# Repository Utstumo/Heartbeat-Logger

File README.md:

# Heartbeat-Logger
A small, portable device that will continuously log your ECG - the "waveform" of your heart - onto a memory card for analysis.

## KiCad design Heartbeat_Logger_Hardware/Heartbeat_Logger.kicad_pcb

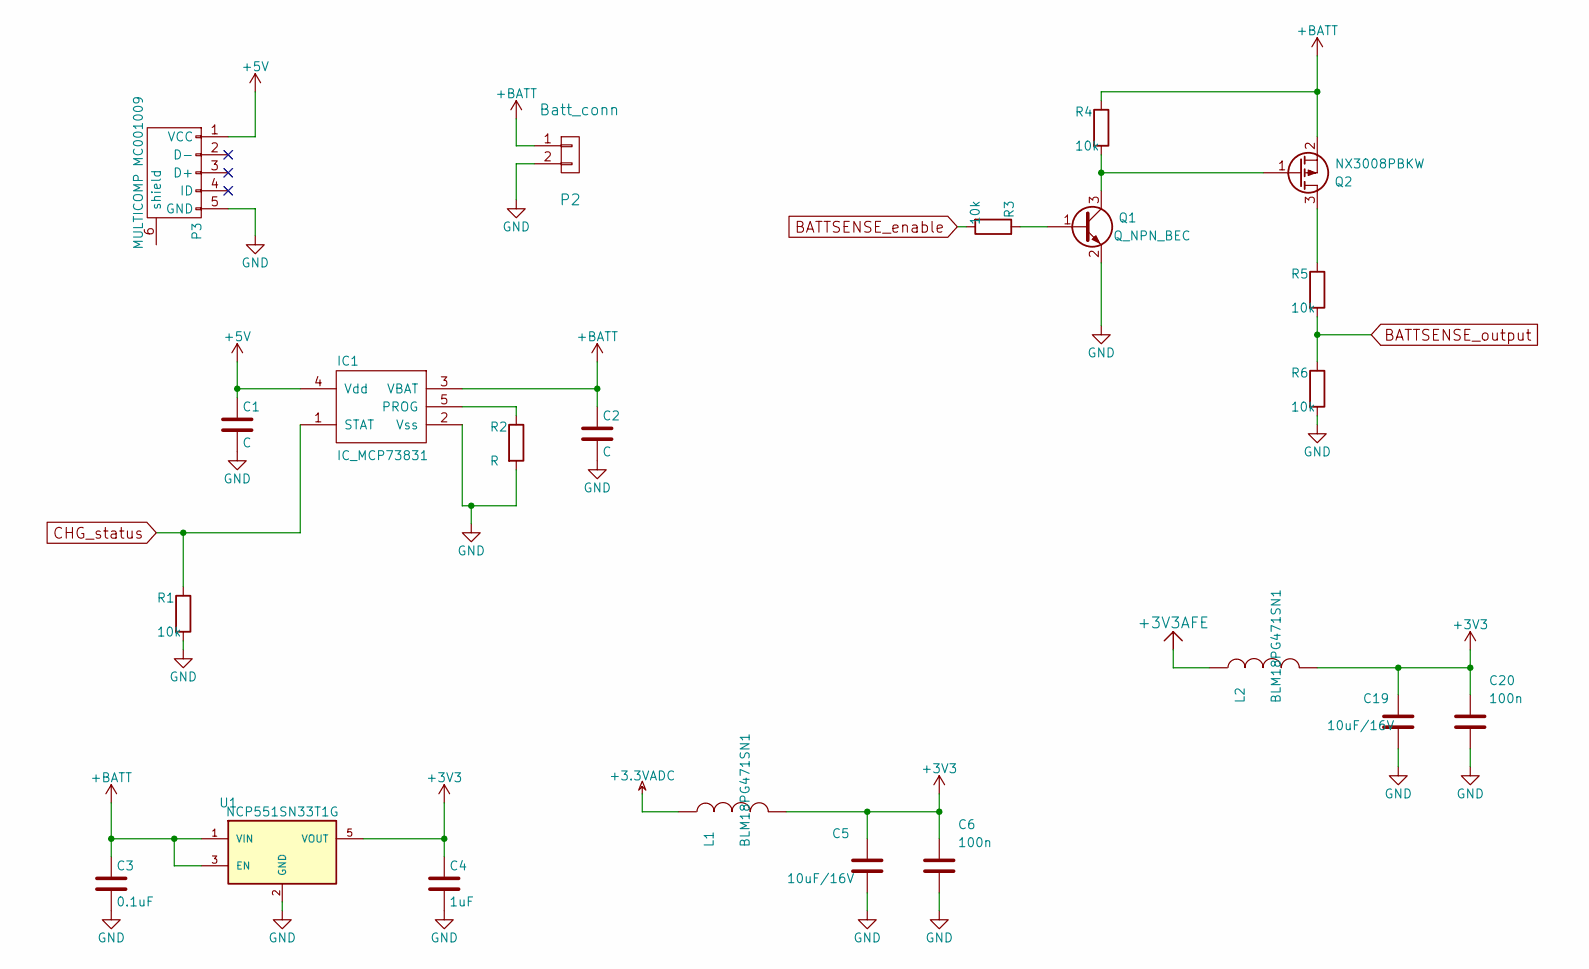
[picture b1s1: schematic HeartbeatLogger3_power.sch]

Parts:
C1, C2: C; C_0603_HandSoldering
C3: 0.1uF; C_0603_HandSoldering
C4: 1uF; C_0603_HandSoldering
C5, C19: 10uF/16V; C_0603_HandSoldering
C6, C20: 100n; C_0603_HandSoldering
IC1: IC_MCP73831; SOT-23-5
L1, L2: BLM18PG471SN1; R_0603_HandSoldering
P2: Batt_conn; Wire_terminal_x2
P3: MULTICOMP MC001009; Multicomp_MC001009_handsolder
Q1: Q_NPN_BEC
Q2: NX3008PBKW; SOT-323
R1, R3, R4, R5, R6: 10k; R_0603_HandSoldering
R2: R; R_0603_HandSoldering
U1: NCP551SN33T1G; SOT-23-5

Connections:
+3.3VADC: L1.1; also elsewhere on the board
+3V3: C4.1, C5.1, C6.1, C19.1, C20.1, L1.2, L2.2, U1.5 (VOUT); also elsewhere on the board
+3V3AFE: L2.1; also elsewhere on the board
+5V: C1.1, IC1.4 (Vdd), P3.1 (VCC)
+BATT: C2.1, C3.1, IC1.3 (VBAT), P2.1, Q2.2 (S), R4.1, U1.1 (VIN), U1.3 (EN)
BATTSENSE_enable: R3.2; also elsewhere on the board
BATTSENSE_output: R5.2, R6.1; also elsewhere on the board
CHG_status: IC1.1 (STAT), R1.1; also elsewhere on the board
GND: C1.2, C2.2, C3.2, C4.2, C5.2, C6.2, C19.2, C20.2, IC1.2 (Vss), P2.2, P3.5 (GND), Q1.2 (E), R1.2, R2.2, R6.2, U1.2 (GND); also elsewhere on the board
unnamed: IC1.5 (PROG), R2.1
unnamed: Q1.1 (B), R3.1
unnamed: Q1.3 (C), Q2.1 (G), R4.2
unnamed: Q2.3 (D), R5.1

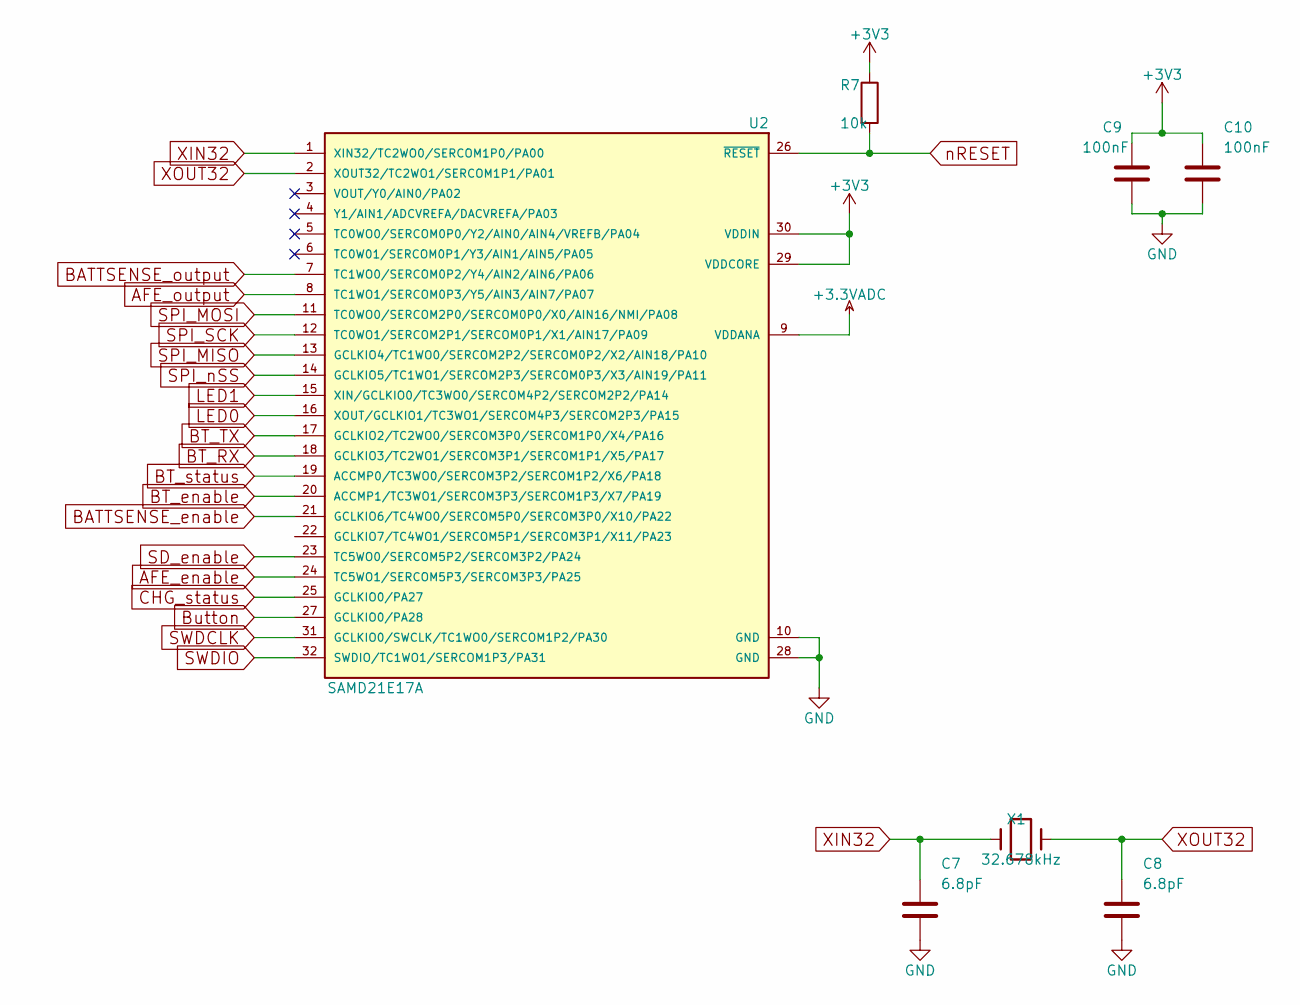
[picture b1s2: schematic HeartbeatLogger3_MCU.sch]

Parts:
C7, C8: 6.8pF; C_0603_HandSoldering
C9, C10: 100nF; C_0603_HandSoldering
R7: 10k; R_0603_HandSoldering
U2: SAMD21E17A; SAMD21_QFP_32_handsolder
X1: XTAL-32.768kHz-Cilindrical-SMD; ABS07-32.768KHZ-T

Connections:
+3.3VADC: U2.9 (VDDANA); also elsewhere on the board
+3V3: C9.1, C10.1, R7.1, U2.29 (VDDCORE), U2.30 (VDDIN); also elsewhere on the board
AFE_enable: U2.24 (TC5WO1/SERCOM5P3/SERCOM3P3/PA25); also elsewhere on the board
AFE_output: U2.8 (TC1WO1/SERCOM0P3/Y5/AIN3/AIN7/PA07); also elsewhere on the board
BATTSENSE_enable: U2.21 (GCLKIO6/TC4WO0/SERCOM5P0/SERCOM3P0/X10/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); also elsewhere on the board
BATTSENSE_output: U2.7 (TC1WO0/SERCOM0P2/Y4/AIN2/AIN6/PA06); also elsewhere on the board
BT_RX: U2.18 (GCLKIO3/TC2WO1/SERCOM3P1/SERCOM1P1/X5/P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); also elsewhere on the board
BT_TX: U2.17 (GCLKIO2/TC2WO0/SERCOM3P0/SERCOM1P0/X4/P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); also elsewhere on the board
BT_enable: U2.20 (ACCMP1/TC3WO1/SERCOM3P3/SERCOM1P3/X7/PA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); also elsewhere on the board
BT_status: U2.19 (ACCMP0/TC3WO0/SERCOM3P2/SERCOM1P2/X6/PA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); also elsewhere on the board
Button: U2.27 (GCLKIO0/PA28); also elsewhere on the board
CHG_status: U2.25 (GCLKIO0/PA27); also elsewhere on the board
GND: C7.2, C8.2, C9.2, C10.2, U2.10 (GND), U2.28 (GND); also elsewhere on the board
LED0: U2.16 (XOUT/GCLKIO1/TC3WO1/SERCOM4P3/SERCOM2P3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); also elsewhere on the board
LED1: U2.15 (XIN/GCLKIO0/TC3WO0/SERCOM4P2/SERCOM2P2/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); also elsewhere on the board
SD_enable: U2.23 (TC5WO0/SERCOM5P2/SERCOM3P2/PA24); also elsewhere on the board
SPI_MISO: U2.13 (GCLKIO4/TC1WO0/SERCOM2P2/SERCOM0P2/X2/A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); also elsewhere on the board
SPI_MOSI: U2.11 (TC0WO0/SERCOM2P0/SERCOM0P0/X0/AIN16/NMI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); also elsewhere on the board
SPI_SCK: U2.12 (TC0WO1/SERCOM2P1/SERCOM0P1/X1/AIN17/PA09); also elsewhere on the board
SPI_nSS: U2.14 (GCLKIO5/TC1WO1/SERCOM2P3/SERCOM0P3/X3/A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); also elsewhere on the board
SWDCLK: U2.31 (GCLKIO0/SWCLK/TC1WO0/SERCOM1P2/PA30); also elsewhere on the board
SWDIO: U2.32 (SWDIO/TC1WO1/SERCOM1P3/PA31); also elsewhere on the board
XIN32: C7.1, U2.1 (XIN32/TC2WO0/SERCOM1P0/PA00), X1.1
XOUT32: C8.1, U2.2 (XOUT32/TC2WO1/SERCOM1P1/PA01), X1.2
nRESET: R7.2, U2.26 (~RESET~); also elsewhere on the board

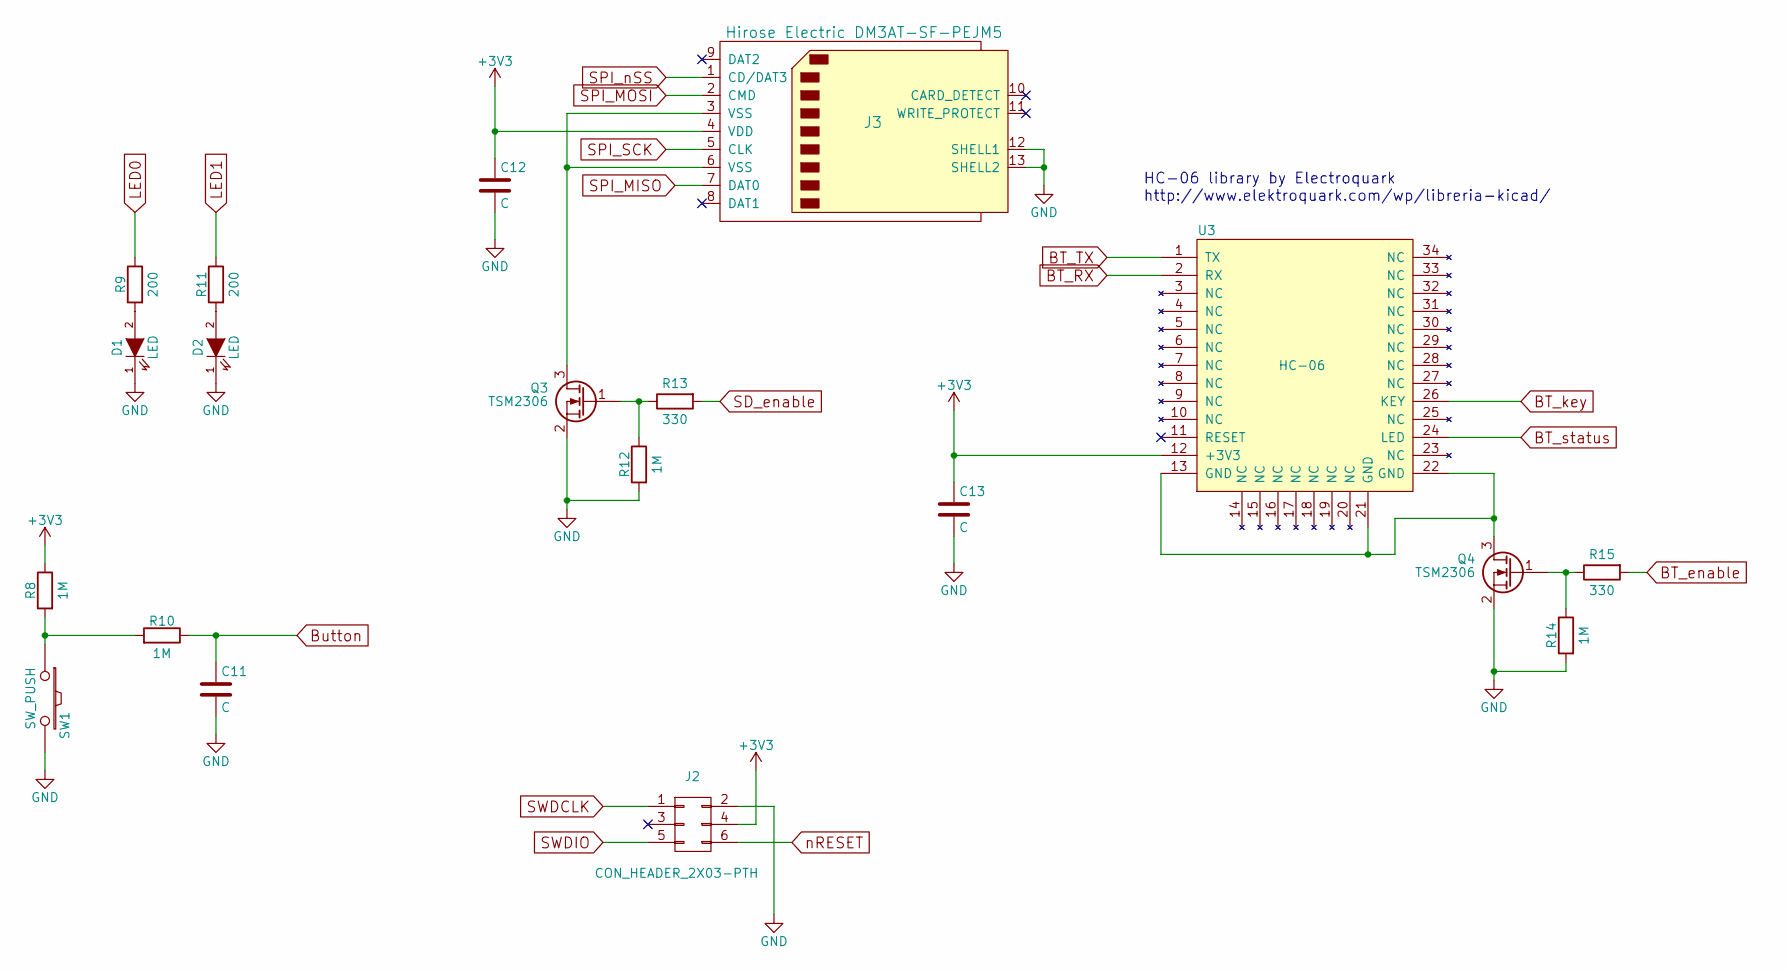
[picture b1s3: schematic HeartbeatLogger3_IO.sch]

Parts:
C11, C12, C13: C; C_0603_HandSoldering
D1, D2: LED; R_0603_HandSoldering
J2: CON_HEADER_2X03-PTH; Pin_Header_Straight_2x03
J3: Hirose Electric DM3AT-SF-PEJM5; Hirose_Electric_DM3AT-SF-PEJM5_handsolder
Q3, Q4: TSM2306; SOT-23
R8, R10, R12, R14: 1M; R_0603_HandSoldering
R9, R11: 200; R_0603_HandSoldering
R13, R15: 330; R_0603_HandSoldering
SW1: SW_PUSH; MC32882
U3: HC-06

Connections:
+3V3: C12.1, C13.1, J2.4, J3.4 (VDD), R8.1, U3.12 (+3V3); also elsewhere on the board
BT_RX: U3.2 (RX); also elsewhere on the board
BT_TX: U3.1 (TX); also elsewhere on the board
BT_enable: R15.2; also elsewhere on the board
BT_status: U3.24 (LED); also elsewhere on the board
Button: C11.1, R10.1; also elsewhere on the board
GND: C11.2, C12.2, C13.2, D1.1 (K), D2.1 (K), J2.2, J3.12 (SHELL1), J3.13 (SHELL2), Q3.2 (S), Q4.2 (S), R12.2, R14.2, SW1.2; also elsewhere on the board
LED0: R9.1; also elsewhere on the board
LED1: R11.1; also elsewhere on the board
unnamed: D1.2 (A), R9.2
unnamed: D2.2 (A), R11.2
unnamed: J3.3 (VSS), J3.6 (VSS), Q3.3 (D)
unnamed: Q3.1 (G), R12.1, R13.1
unnamed: Q4.1 (G), R14.1, R15.1
unnamed: Q4.3 (D), U3.13 (GND), U3.21 (GND), U3.22 (GND)
unnamed: R8.2, R10.2, SW1.1
SD_enable: R13.2; also elsewhere on the board
SPI_MISO: J3.7 (DAT0); also elsewhere on the board
SPI_MOSI: J3.2 (CMD); also elsewhere on the board
SPI_SCK: J3.5 (CLK); also elsewhere on the board
SPI_nSS: J3.1 (CD/DAT3); also elsewhere on the board
SWDCLK: J2.1; also elsewhere on the board
SWDIO: J2.5; also elsewhere on the board
nRESET: J2.6; also elsewhere on the board

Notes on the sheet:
HC-06 library by Electroquark http://www.elektroquark.com/wp/libreria-kicad/

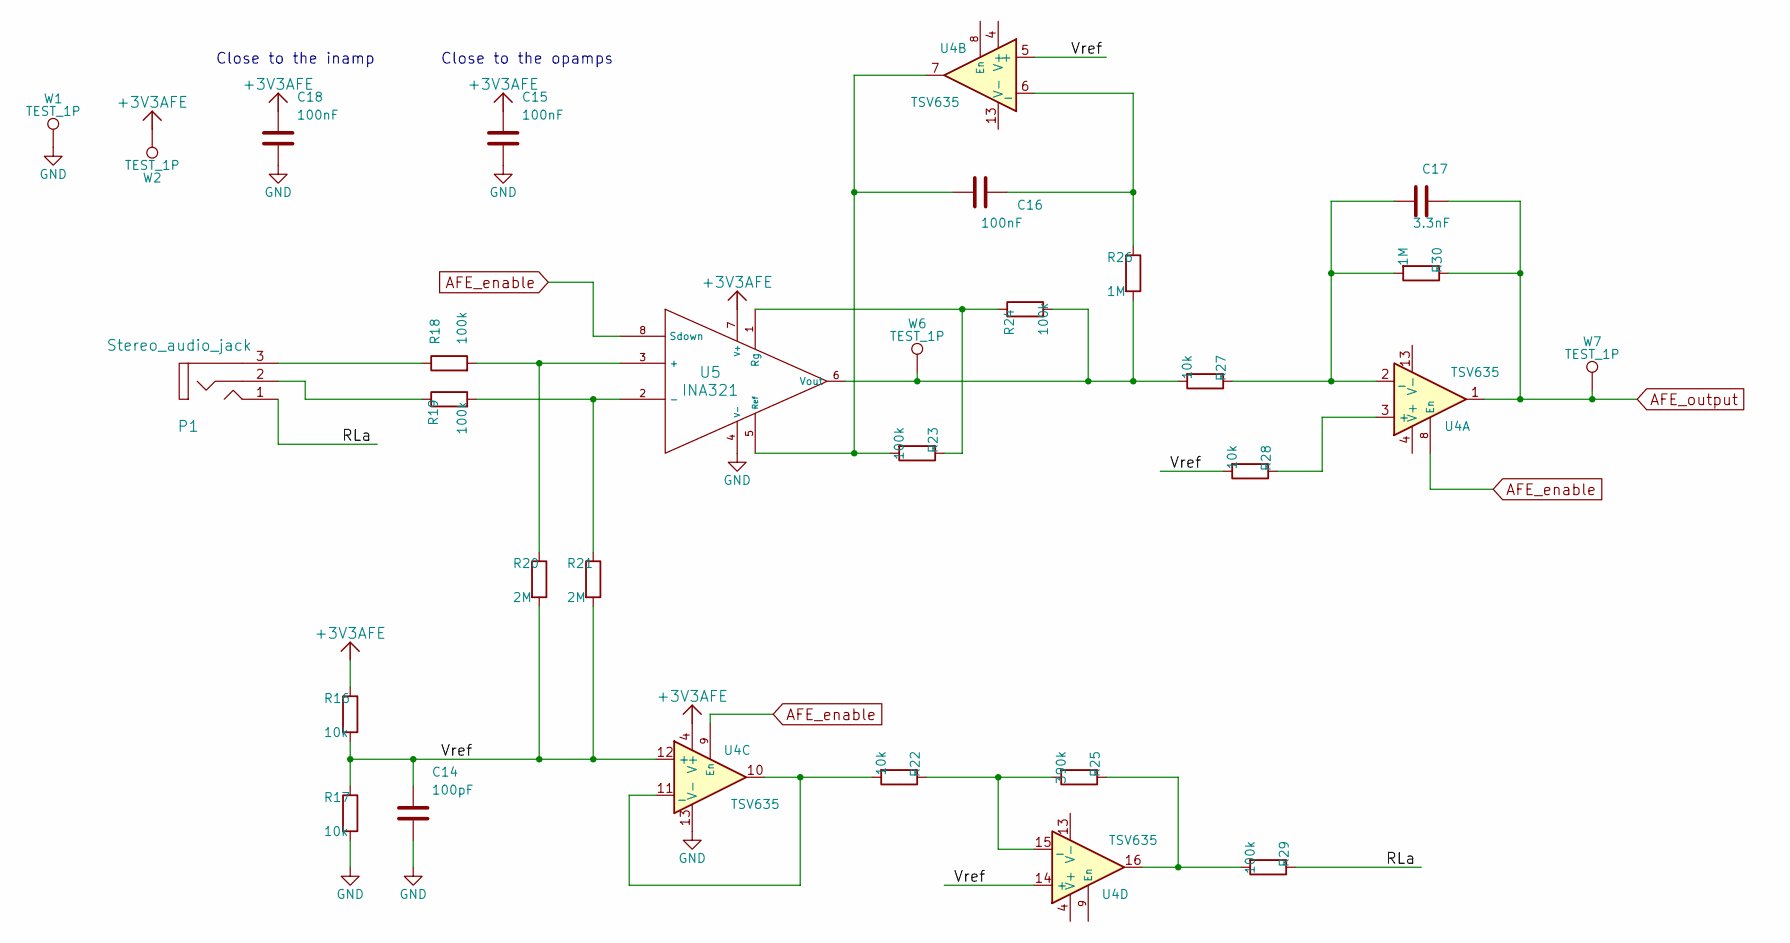
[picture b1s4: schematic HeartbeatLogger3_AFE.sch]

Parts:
C14: 100pF; C_0603_HandSoldering
C15, C16, C18: 100nF; C_0603_HandSoldering
C17: 3.3nF; C_0603_HandSoldering
P1: Stereo_audio_jack; Multicomp_MJ4435-R
R16, R17, R22, R27, R28: 10k; R_0603_HandSoldering
R18, R19, R23, R24, R29: 100k; R_0603_HandSoldering
R20, R21: 2M; R_0603_HandSoldering
R25: 390k; R_0603_HandSoldering
R26, R30: 1M; R_0603_HandSoldering
U4: TSV635; TSV635_TSSOP16
U5: INA321; INA321_MSOP8
W1, W2, W6, W7: TEST_1P; R_0603

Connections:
+3V3AFE: C15.1, C18.1, R16.1, U4.4 (V+), U5.7 (V+), W2.1; also elsewhere on the board
/AFE/RLa: P1.1, R29.1
/AFE/Vref: C14.1, R16.2, R17.1, R20.2, R21.2, R28.2, U4.5 (+), U4.12 (+), U4.14 (+)
AFE_enable: U4.8 (En), U4.9 (En), U5.8 (Sdown); also elsewhere on the board
AFE_output: C17.1, R30.1, U4.1, W7.1; also elsewhere on the board
GND: C14.2, C15.2, C18.2, R17.2, U4.13 (V-), U5.4 (V-), W1.1; also elsewhere on the board
unnamed: C16.1, R26.1, U4.6 (_)
unnamed: C16.2, R23.2, U4.7, U5.5 (Ref)
unnamed: C17.2, R27.1, R30.2, U4.2 (_)
unnamed: P1.2, R19.1
unnamed: P1.3, R18.1
unnamed: R18.2, R20.1, U5.3 (+)
unnamed: R19.2, R21.1, U5.2 (-)
unnamed: R22.1, R25.2, U4.15 (_)
unnamed: R22.2, U4.10, U4.11 (_)
unnamed: R23.1, R24.1, U5.1 (Rg)
unnamed: R24.2, R26.2, R27.2, U5.6 (Vout), W6.1
unnamed: R25.1, R29.2, U4.16
unnamed: R28.1, U4.3 (+)

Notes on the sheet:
Close to the opamps
Close to the inamp

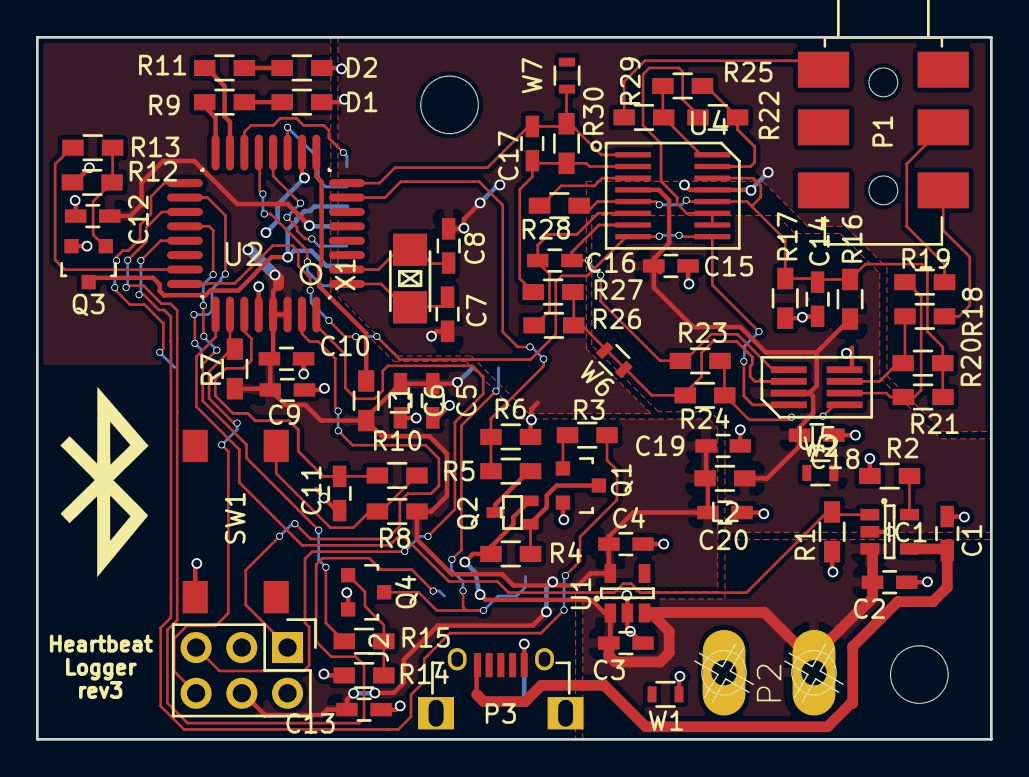
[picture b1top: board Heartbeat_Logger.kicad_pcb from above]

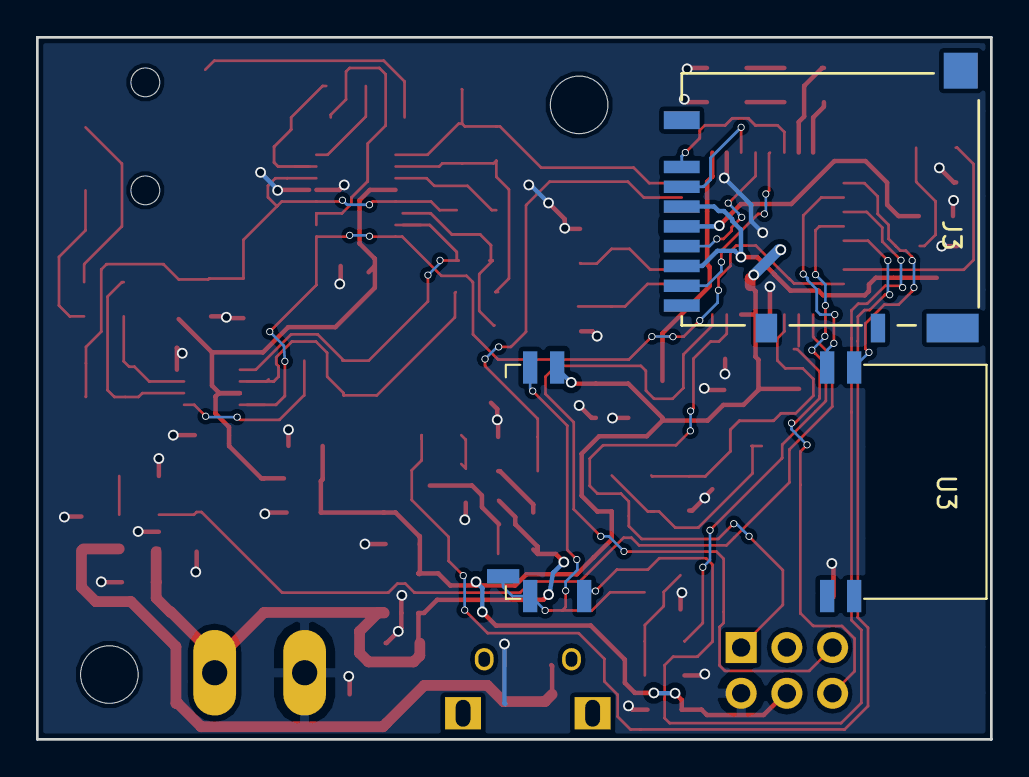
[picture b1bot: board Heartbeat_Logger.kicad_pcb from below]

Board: 2 copper layers, 53.0 x 39.0 mm, 75 parts (2 on the bottom side), 54 nets.

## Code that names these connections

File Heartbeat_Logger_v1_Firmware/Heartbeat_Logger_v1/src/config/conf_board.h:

/**
 * \file
 *
 * \brief User board configuration template
 *
 * Copyright (C) 2012-2015 Atmel Corporation. All rights reserved.
 *
 * \asf_license_start
 *
 * \page License
 *
 * Redistribution and use in source and binary forms, with or without
 * modification, are permitted provided that the following conditions are met:
 *
 * 1. Redistributions of source code must retain the above copyright notice,
 *    this list of conditions and the following disclaimer.
 *
 * 2. Redistributions in binary form must reproduce the above copyright notice,
 *    this list of conditions and the following disclaimer in the documentation
 *    and/or other materials provided with the distribution.
 *
 * 3. The name of Atmel may not be used to endorse or promote products derived
 *    from this software without specific prior written permission.
 *
 * 4. This software may only be redistributed and used in connection with an
 *    Atmel microcontroller product.
 *
 * THIS SOFTWARE IS PROVIDED BY ATMEL "AS IS" AND ANY EXPRESS OR IMPLIED
 * WARRANTIES, INCLUDING, BUT NOT LIMITED TO, THE IMPLIED WARRANTIES OF
 * MERCHANTABILITY, FITNESS FOR A PARTICULAR PURPOSE AND NON-INFRINGEMENT ARE
 * EXPRESSLY AND SPECIFICALLY DISCLAIMED. IN NO EVENT SHALL ATMEL BE LIABLE FOR
 * ANY DIRECT, INDIRECT, INCIDENTAL, SPECIAL, EXEMPLARY, OR CONSEQUENTIAL
 * DAMAGES (INCLUDING, BUT NOT LIMITED TO, PROCUREMENT OF SUBSTITUTE GOODS
 * OR SERVICES; LOSS OF USE, DATA, OR PROFITS; OR BUSINESS INTERRUPTION)
 * HOWEVER CAUSED AND ON ANY THEORY OF LIABILITY, WHETHER IN CONTRACT,
 * STRICT LIABILITY, OR TORT (INCLUDING NEGLIGENCE OR OTHERWISE) ARISING IN
 * ANY WAY OUT OF THE USE OF THIS SOFTWARE, EVEN IF ADVISED OF THE
 * POSSIBILITY OF SUCH DAMAGE.
 *
 * \asf_license_stop
 *
 */
/*
 * Support and FAQ: visit <a href="http://www.atmel.com/design-support/">Atmel Support</a>
 */

#ifndef CONF_BOARD_H
#define CONF_BOARD_H

#define F_CPU 1000000UL

#define SD_MOSI_PIN PIN_PA09
#define SD_MISO_PIN PIN_PA08
#define SD_CLK_PIN PIN_PA10
#define SD_SS_PIN PIN_PA11
#define SD_EN_PIN PIN_PA24
#define SD_DETECT_PIN PIN_PA15

//LEDs
#define RLED_PIN PIN_PA05
#define GLED_PIN PIN_PA06

//Other digital
#define EXT_ENABLE_PIN PIN_PA19
#define EXT_STATUS_PIN PIN_PA18
#define BATTSENSE_ENABLE_PIN PIN_PA22
#define CHG_STATUS_PIN PIN_PA23
#define SDCARD_ENABLE_PIN PIN_PA24
#define AFE_ENABLE_PIN PIN_PA27

//Analog
#define SIGNAL_PIN PIN_PA03
#define SIGNAL_ADC_INPUT ADC_POSITIVE_INPUT_PIN1
#define BATTSENSE_PIN PIN_PA02
#define BATTSENSE_ADC_INPUT ADC_POSITIVE_INPUT_PIN2

//Switch
#define SW0_PIN PIN_PA07
#define SW0_ACTIVE                false
#define SW0_INACTIVE              !SW0_ACTIVE
#define SW0_EIC_PIN               PIN_PA07A_EIC_EXTINT7
#define SW0_EIC_MUX               MUX_PA07A_EIC_EXTINT7
#define SW0_EIC_PINMUX            PINMUX_PA07A_EIC_EXTINT7
#define SW0_EIC_LINE              7


#define CHG_EIC_PIN               PIN_PA23A_EIC_EXTINT7
#define CHG_EIC_MUX               MUX_PA23A_EIC_EXTINT7
#define CHG_EIC_PINMUX            PINMUX_PA23A_EIC_EXTINT7
#define CHG_EIC_LINE              7


#endif // CONF_BOARD_H

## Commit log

2016-05-12 Initial commit
    The Heartbeat Logger firmware. See the project details on
    https://hackaday.io/project/7651-heartbeat-logger
2017-01-28 Added hardware files
2017-01-28 Update license
